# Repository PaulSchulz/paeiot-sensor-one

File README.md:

# paeiot-sensor-one
  PAE IoT LoRaWAN Sensor Module

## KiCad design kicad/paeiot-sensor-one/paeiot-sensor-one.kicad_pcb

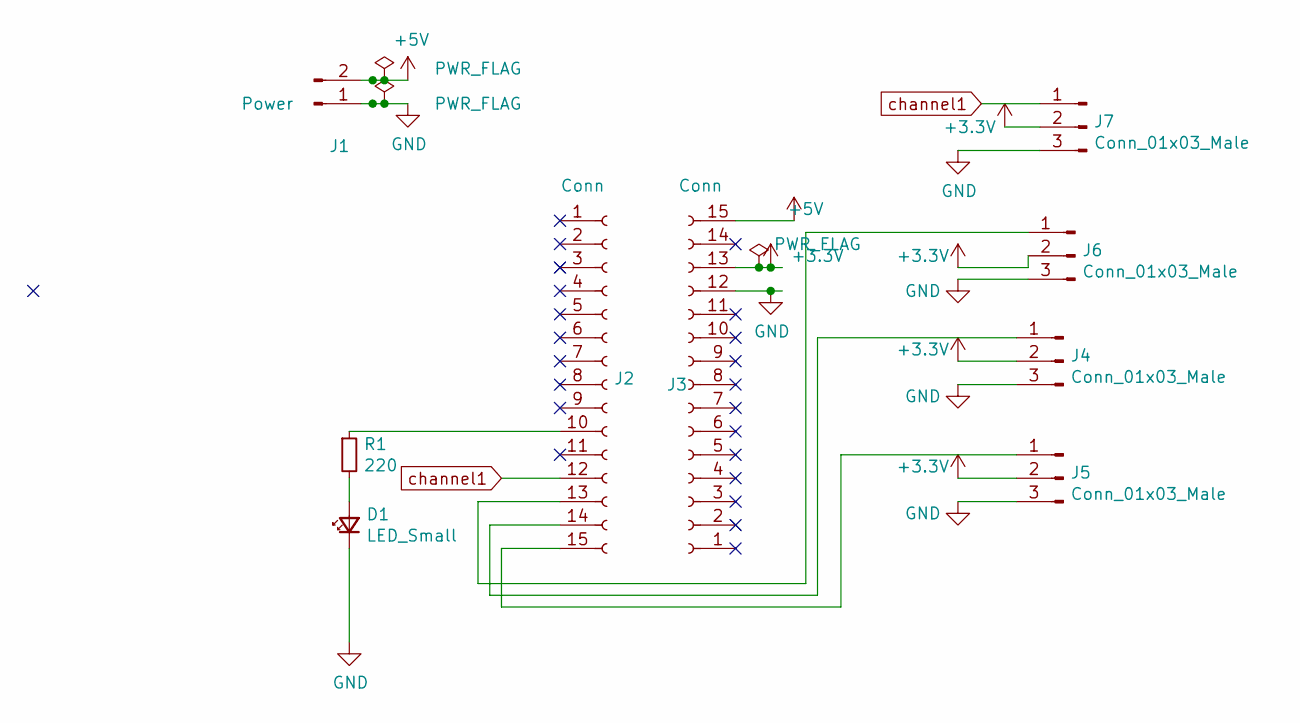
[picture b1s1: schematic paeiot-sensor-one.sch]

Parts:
D1: LED_Small; LED_D3.0mm
J1: Power; PinHeader_1x02_P2.54mm_Horizontal
J2, J3: Conn; PinHeader_1x15_P2.54mm_Vertical
J4, J5, J6, J7: Conn_01x03_Male; PinHeader_1x03_P2.54mm_Horizontal
R1: 220; R_Axial_DIN0309_L9.0mm_D3.2mm_P2.54mm_Vertical

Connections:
+3V3: J3.13, J4.2, J5.2, J6.2, J7.2
+5V: J1.2, J3.15
GND: D1.1 (K), J1.1, J3.12, J4.3, J5.3, J6.3, J7.3
unnamed: D1.2 (A), R1.2
unnamed: J2.10, R1.1
unnamed: J2.13, J6.1
unnamed: J2.14, J4.1
unnamed: J2.15, J5.1
channel1: J2.12, J7.1

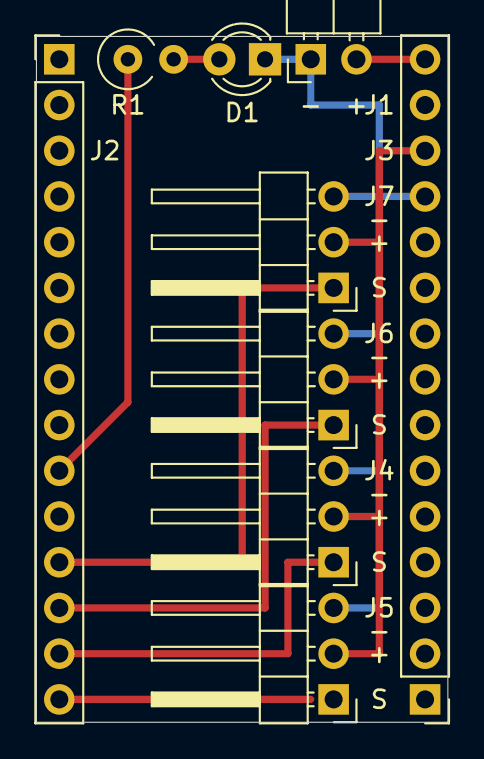
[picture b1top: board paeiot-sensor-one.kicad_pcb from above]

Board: 2 copper layers, 22.9 x 38.1 mm, 9 parts (0 on the bottom side), 9 nets.

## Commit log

2021-08-05 doc: Add blog and images
2021-08-05 doc: Minor change (imagew fix)
2021-08-05 doc: Minor change (image fix)
2021-08-05 doc: Add more details to progress report
2021-08-05 doc: Updates progress report
2021-08-05 doc: Updates images
2021-08-05 arduino: Rename sketch directory
2021-08-05 arduino: Adds .gitignore to remove arduino_secrets.h from commits
2021-08-05 Arduino: Removed .gitignore
2021-08-05 doc: Updates description
2021-08-05 stl: Adds baseplate STL files
2021-08-05 stl: Fixes Typo
2021-08-05 stl: Adds link to TinkerCAD
2021-08-12 stl: Updates after first round of 3D printing
    - Added hole for MKRWAN1310 pins.
    - Added baseplate mounting holes M4 (assumed).
    - Added cutout for glands.
2021-08-14 stl: Move/fix corner cutout on base plate
2021-08-14 fritzing: Adds initial wirign diagram
2021-08-14 blog: Adds status update
2021-08-14 fritzing: Fixes circuit and board routing
2021-08-14 fritzing: Adds componet sources
2021-08-14 blog: Fixes date in title
2021-08-14 blog: Updates blog index
2021-08-28 blog: Add status update
2021-08-28 blog: Updates blog post and blog index
2021-08-28 blog: Updates images for blog post
2021-08-30 fritzing: Created v1.0 of the printed circuit board
    Supports two temperature/humidity sensors.
2021-09-21 friting: (Minor) Finessing the board layout
2021-09-21 fritzing: (minor) Fix PCB screen (remove extra label)
2021-10-02 fritzing: Fixes issues with PCB board
    - Uses new Fritzing template file (for MKRWAN1300) as previous ones
    did not have a correct PCB template.
    Downloaded from: https://forum.fritzing.org/t/arduino-mkr-wan-1300/6317/8
2021-10-02 Arduino: Removes serial initialisation check, which halts reset
    The original code checked to see whether the USB serial connected during
    initialisation process. This is a problem when the sensor need to reboot and it
    is not connected to anything.
2021-10-02 blog: Update progress report
2021-10-09 doc: Added bill-of-materials
2021-10-09 Arduino:(minor) Fixes code ater merge
2021-10-09 friting:minor Adds fritzing file back in
2021-10-09 blog: Adds new blog post
    Added in a new branch for reviewing.
2021-10-09 blog: Minor fixes
2021-10-09 blog: Updates image
2021-10-29 arduino: Expands number of sensor channels to 4
    Version 1.2
    Lots of fixes and changes
    - 4 channels for temperature/humidity sensors
    - Improved serial status output
    - Status LED flashes when transmitting
    - Code added for formatting/processing data
2021-10-29 blog: Add status report 20211030
2021-10-29 blog: Updates to status report
2021-10-30 blog: Adds minor fix
2021-10-30 blog: Adds images to status report
2021-10-30 blog: Updates image file
2021-11-08 kicad: Adds initial schematic and board layout in KiCAD
2021-11-12 README: Add image
2021-11-12 README: Update READEM with images
2022-01-11 blog: First Status Update for 2022
2022-01-11 blog: Fix image name
2022-01-11 blog: Update index
2022-01-11 blog: Update next steps
2022-01-12 blog: Add more details
2022-01-19 blog: Add blog post for 20211113
    This commit was somehow missed.
2022-01-19 blog: Fix up some formatting
2022-01-19 blog: Quick status report on Indoor Enclosure sub-project
2022-01-19 blog: Minor workding fix
2022-01-19 blog: Re-edit blog post
2022-01-19 blog: Minor edit to blog post
2022-01-19 blog: Add link to data image
2022-01-19 blog: Fix image link
2022-01-20 blog: Add some more details about the build of the system
2022-01-20 README: Update with newer image of inside enclosure
2022-01-20 README: Add some more links
2022-01-20 README: Update links and License information
2022-01-20 blog: Add additional video link
2022-03-22 blog: Added sensor update
2022-03-22 blog: Updates/fixes
2022-03-22 blog: Minor update
2022-06-16 blog: Add blog post for 20220616
2022-06-16 blog: minor fix
2022-07-15 blog: Added procedure for hardware setup
2022-07-16 Arduino: Added AU915 version of FirstConfiguration script
    Modifications have been made to the MKRWAN1310 to work with the public
    Australian LoRaWAN network.
2022-07-16 Arduino: Add MKRWANFWUpdate_standalone sketch - ARD-078 1.2.3
    Add the sketch from MKRWAN library examples for revision control. Compile and
    install and run this sketch to upgrade the MKRWAN1310 LoRa Firmware to the
    version:
    ARD-078 1.2.3
    This sketch will run and reinstall the firmware whenever the MKRWAN1310 board is
    powered on, so replace with another sketch once firmware upgrade has been done.
2022-07-16 Arduino: WIP v1.3.1 - Updates to paeiot-sensor-one
    - Added Watchdog code.
    - Started refactoring code into separate 'setup' and 'loop' sections for
    different sensors and features.
2022-07-18 Arduino: WIP v1.3.3rc1 - Added Power Monitoring code
    Also, refactored the original DHT code into 'setup' and 'loop' functions.
    Dummy temperature and humidity reading are being sent.
2022-07-19 Arduino: WIP v1.2.2pre1 - Refactoring sensor code
    Putting code for various sensors into their own _setup and _loop functions.
2022-07-21 Arduino: WIP v1.3.3pre2 - Detecting and sending DHT sensor data
2022-07-23 Arduino: WIP v1.3.3pre2 - Bump version to test compile
2022-07-23 Arduino: WIP v1.3.4pre2 Refactor to remove dependency on DHT code
2022-07-26 Arduino: WIP v1.3.4pre3 - Fix AD voltage calculation
    Added some debugging code that can be removed later. Just sends raw AD counts
    for verification.
    Added code so that the A2D resolution can be adjusted (higher) if
    required.
2022-07-27 Arduino: WIP v1.3.4pre4 - Adjust test data values for SCD30
    If the SCD30 sensor hardware is not detected when the SCD30 feature is enabled,
    the unit will transmit test data instead.
    To make it more obvious that this is test data (other than it not changing over
    time) to values have been chosen to be:
    Temperature = 0.0 degC
    Relative Humidity = 0.0 %
2022-07-31 Arduino: v1.4.0pre1 - Minor fixes
    Feature complete for data acquisition.
2022-09-01 v1.4.1: Change delay to use low power sleep
    Reprogramming won't work when in sleep mode (getting errors) but there is
    sufficient delay on boot to allow USB loader to take control. So, hit reset on
    the board before hitting the 'compile and program' button on the Arduino IDE.
2022-09-20 blog: Added progress report for 2022-09-21
2022-09-20 blog: Fix index
2022-09-20 blog: Minor edit
2022-10-17 doc: Add Arduino Sketch design description documentation
